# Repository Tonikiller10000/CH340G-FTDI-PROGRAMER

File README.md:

# CH340G-FTDI-PROGRAMER

## FTDI Programmer V2.0
An UART microcontroller programmer using CH340G IC. UART stands for Universal Asynchronous reciver/transmiter Protocol and it works like this:
The communication beggin with a start bit, continue with a data frame of 5 to 9 bits and an optional parity bit to check the sent data integrity, and ends with 1 or 2 stop bits.

## How it works:
The CH340G ic transform the UART signal into USB signal and the other way around. For it to work, it needs an 12 MHz crystal oscilator and 2 capacitors, 2x 1K protection resistors. For 5V operation, pin 4 is connected to a 4.7-20nF ceramic decouplig capacitor to GND, and for 3.3V operation, it connects dirrectly to VCC. The FTDI programmer is recognised dirrectly by the computer and does not need any additional driver.
The USB data pins connect dirrectly to each other (D+ to D+ and D- to D-)

### CH340G pinout
<table>
  <tr><td>Nr.</td>   <td>Name</td>   <td>Function</td>                                                  </tr>
  <tr><td>1</td>     <td>GND</td>    <td>Ground reference of the chip.</td>                             </tr>
  <tr><td>2</td>     <td>TXD</td>    <td>UART Data Transmit output.</td>                                </tr>          
  <tr><td>3</td>     <td>RXD</td>    <td>UART Data Receive input.</td>                                  </tr>          
  <tr><td>4</td>     <td>V3</td>     <td>3.3V internal reference for USB. </td>                         </tr>          
  <tr><td>5</td>     <td>UD+</td>    <td>USB D+ signal.</td>                                            </tr>          
  <tr><td>6</td>     <td>UD-</td>    <td>USB D- signal.</td>                                            </tr>          
  <tr><td>7</td>     <td>XII</td>    <td>Crystal oscillator input.</td>                                 </tr>          
  <tr><td>8</td>     <td>XO</td>     <td>Output of the crystal oscillator.</td>                         </tr>          
  <tr><td>9</td>     <td>CTS</td>    <td>UART flow control signal Clear to Send.</td>                   </tr>          
  <tr><td>10</td>    <td>DSR</td>    <td>UART flow control signal Data Set Ready.</td>                  </tr>          
  <tr><td>11</td>    <td>RI</td>     <td>UART flow control signal Ring In.</td>                         </tr>          
  <tr><td>12</td>    <td>DCD</td>    <td>UART flow control signal Data Carrier Detect.</td>             </tr>          
  <tr><td>13</td>    <td>DTR</td>    <td>UART flow control signal Data Terminal Ready.</td>             </tr>          
  <tr><td>14</td>    <td>RTS</td>    <td>UART flow control signal Request to Send.</td>                 </tr>          
  <tr><td>15</td>    <td>R232</td>   <td>Auxiliary RS232 enable. Active high, internal pull down.</td>  </tr>          
  <tr><td>16</td>    <td>VCC</td>    <td>PowerSupply rail for the chip.</td>                            </tr>          
</table>

> [!NOTE]
> When programming a device, the Tx pin of the programmer conect\`s to the device Rx pin and the Rx of the programmer to the Tx of the device.

## FTDI Programmer V2.1
This is a new design witch includes an [3.3V voltage regulator on the back of the board](https://github.com/Tonikiller10000/CH340G-FTDI-PROGRAMER/blob/main/FtdiProgramer_Pictures/ss3.png) to be used on the 3.3V devices programming. It also has some other pins pulled out to be able to program stuff trouth the serial port. <br>
To select between the 5V and 3.3V modes, an pin jumper cap is used. 

## Links: 
- CH340G Datasheet1: https://pdf1.alldatasheet.com/datasheet-pdf/view/1132618/ETC2/CH340G.html
- CH340G Datasheet2: https://www.mpja.com/download/35227cpdata.pdf
- target: https://github.com/Tonikiller10000/CH340G-FTDI-PROGRAMER/blob/main/FtdiProgramer_Pictures/target.png
- proof of work V1: https://github.com/Tonikiller10000/CH340G-FTDI-PROGRAMER/blob/main/FtdiProgramer_Pictures/ProofOfWorkV1/

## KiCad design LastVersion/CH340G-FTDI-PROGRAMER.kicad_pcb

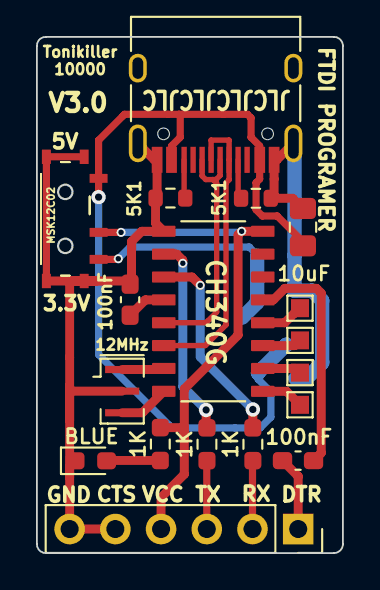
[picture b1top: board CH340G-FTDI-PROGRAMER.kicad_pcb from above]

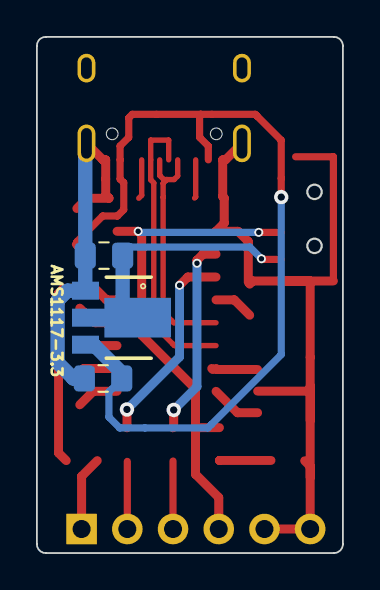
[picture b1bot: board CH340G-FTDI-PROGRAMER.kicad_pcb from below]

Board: 2 copper layers, 17.0 x 28.7 mm, 17 parts (3 on the bottom side), 18 nets.

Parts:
C1, C2, C5: 10uF; C_0805_2012Metric_Pad1.18x1.45mm_HandSolder
C3, C4: 100nF; C_0603_1608Metric_Pad1.08x0.95mm_HandSolder
D1: BLUE; LED_0603_1608Metric_Pad1.05x0.95mm_HandSolder
J2: USB_C_USB2.0; USB_C_Receptacle_HRO_TYPE-C-31-M-12
J4: Conn_01x06_Pin; PinSocket_1x06_P2.54mm_Vertical
R1, R2, R3: 1K; R_0603_1608Metric_Pad0.98x0.95mm_HandSolder
R4, R5: 5K1; R_0603_1608Metric
SW1: MSK12C02
U1: AMS1117-3.3; PK(R-PSSO-F3)
U3: CH340G; SOIC127P600X180-16N
Y1: 12MHz; Resonator_SMD_Murata_CSTxExxV-3Pin_3.0x1.1mm

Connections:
+3.3V: C2.1, SW1.C1 (NO), U1.2 (VO)
+5V: C1.1, C5.1, J2.A4 (VBUS), J2.B4 (VBUS), SW1.A1 (NC), U1.3 (VI)
GND: C1.2, C2.2, C3.2, C5.2, D1.1 (K), J2.A1 (GND), J2.B1 (GND), J2.S1 (SHIELD), J4.5, J4.6, R4.2, R5.2, SW1.MP1, SW1.MP2, SW1.MP3, SW1.MP4, U1.1 (GND), U3.1 (GND), Y1.2
unnamed: D1.2 (A), R1.2
unnamed: J2.A5 (CC1), R4.1
unnamed: J2.B5 (CC2), R5.1
unnamed: C4.1, J4.1
unnamed: J4.2, R3.1
unnamed: J4.3, R2.1
unnamed: R3.2, U3.3 (RXD)
unnamed: R2.2, U3.2 (TXD)
unnamed: J2.A6 (D+), J2.B6 (D+), U3.5 (UD+)
unnamed: J2.A7 (D-), J2.B7 (D-), U3.6 (UD-)
unnamed: C3.1, U3.4 (V3)
unnamed: U3.7 (XI), Y1.1
unnamed: U3.8 (XO), Y1.3
unnamed: C4.2, U3.13 (~DTR)
VCC: J4.4, R1.1, SW1.B1 (COM), U3.16 (VCC)

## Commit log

2023-09-21 CH340G FTDI Programmer V2.0
    The board is ready to order, but I can`t order it rigth now, so I will have to wait about 2 months to finish this project permanently.
    So the last version had the D+ and D- reversed, IDK how I did that, and more than that, I inversed the TX and RX pins and not realy. Iconnected the atmega tx to an conexion named rx, expecting ro con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
    In all that tests I saw that the 100nF capacitor at the DTR is not necesarry, and it could be just a wire in it`s place, and more than that, could be added some desi
